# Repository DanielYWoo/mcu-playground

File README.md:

# Projects

## Arduino Robot with RF24L01 remote control

- arduino-robot-1 for the robot
- arduino-robot-1-rc for the remote controller

## Auto watering system

- arduino-watering-1

## Otto (zhamao)

- arduino-zhamao

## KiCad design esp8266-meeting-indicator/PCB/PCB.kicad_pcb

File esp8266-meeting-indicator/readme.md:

## pins

LED:
two 74HC595N
- D0 to 11, shift clock
- D1 to 12, storage latch
- D2 to 14, serial data input

# LED matrix pins
https://www.hackster.io/shahbaz75sb/8x8-led-matrix-interfacing-with-arduino-daec65

Sound Sensor
- D3

Buzzer
- D4

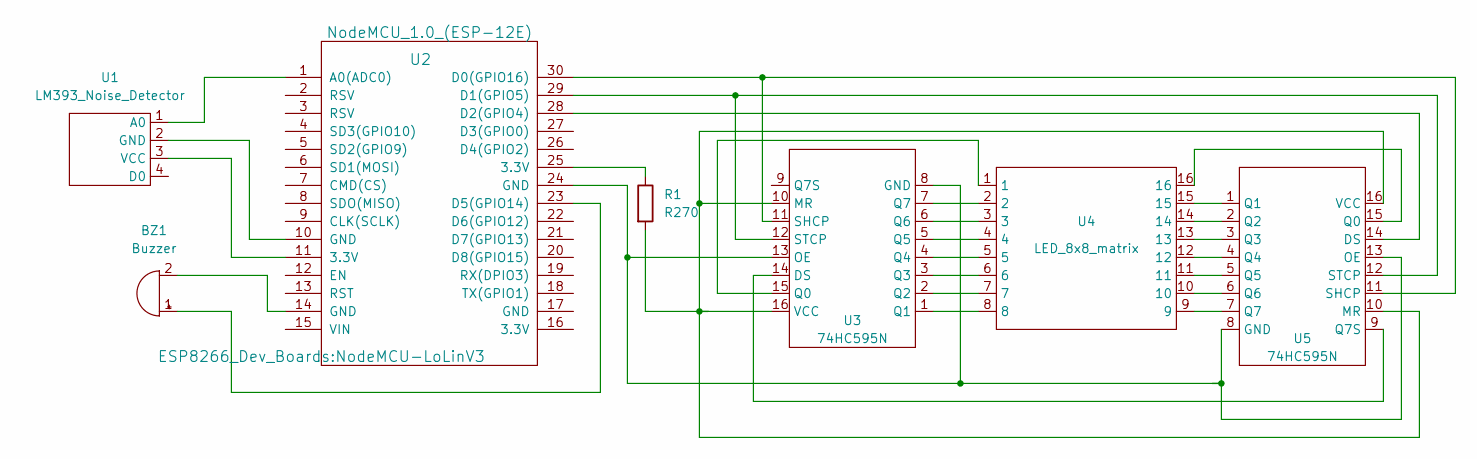
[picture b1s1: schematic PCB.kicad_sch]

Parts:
BZ1: Buzzer; Buzzer_12x9.5RM7.6
R1: R270; R_Axial_DIN0207_L6.3mm_D2.5mm_P10.16mm_Horizontal
U1: LM393_Noise_Detector; PinSocket_1x04_P2.54mm_Vertical
U2: NodeMCU_1.0_(ESP-12E); NodeMCU-LoLinV3
U3, U5: 74HC595N; DIP-16_W7.62mm
U4: LED_8x8_matrix; LED_Matrix_1088

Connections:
unnamed: BZ1.1 (-), U2.23 (D5(GPIO14))
unnamed: BZ1.2 (+), U2.14 (GND)
unnamed: R1.1, U2.25 (3.3V)
unnamed: R1.2, U3.10 (MR), U3.16 (VCC), U5.10 (MR), U5.16 (VCC)
unnamed: U1.1 (A0), U2.1 (A0(ADC0))
unnamed: U1.2 (GND), U2.10 (GND)
unnamed: U1.3 (VCC), U2.11 (3.3V)
unnamed: U2.24 (GND), U3.8 (GND), U3.13 (OE), U5.8 (GND), U5.13 (OE)
unnamed: U2.28 (D2(GPIO4)), U5.14 (DS)
unnamed: U2.29 (D1(GPIO5)), U3.12 (STCP), U5.12 (STCP)
unnamed: U2.30 (D0(GPIO16)), U3.11 (SHCP), U5.11 (SHCP)
unnamed: U3.1 (Q1), U4.8
unnamed: U3.2 (Q2), U4.7
unnamed: U3.3 (Q3), U4.6
unnamed: U3.4 (Q4), U4.5
unnamed: U3.5 (Q5), U4.4
unnamed: U3.6 (Q6), U4.3
unnamed: U3.7 (Q7), U4.2
unnamed: U3.14 (DS), U5.9 (Q7S)
unnamed: U3.15 (Q0), U4.1
unnamed: U4.9, U5.7 (Q7)
unnamed: U4.10, U5.6 (Q6)
unnamed: U4.11, U5.5 (Q5)
unnamed: U4.12, U5.4 (Q4)
unnamed: U4.13, U5.3 (Q3)
unnamed: U4.14, U5.2 (Q2)
unnamed: U4.15, U5.1 (Q1)
unnamed: U4.16, U5.15 (Q0)

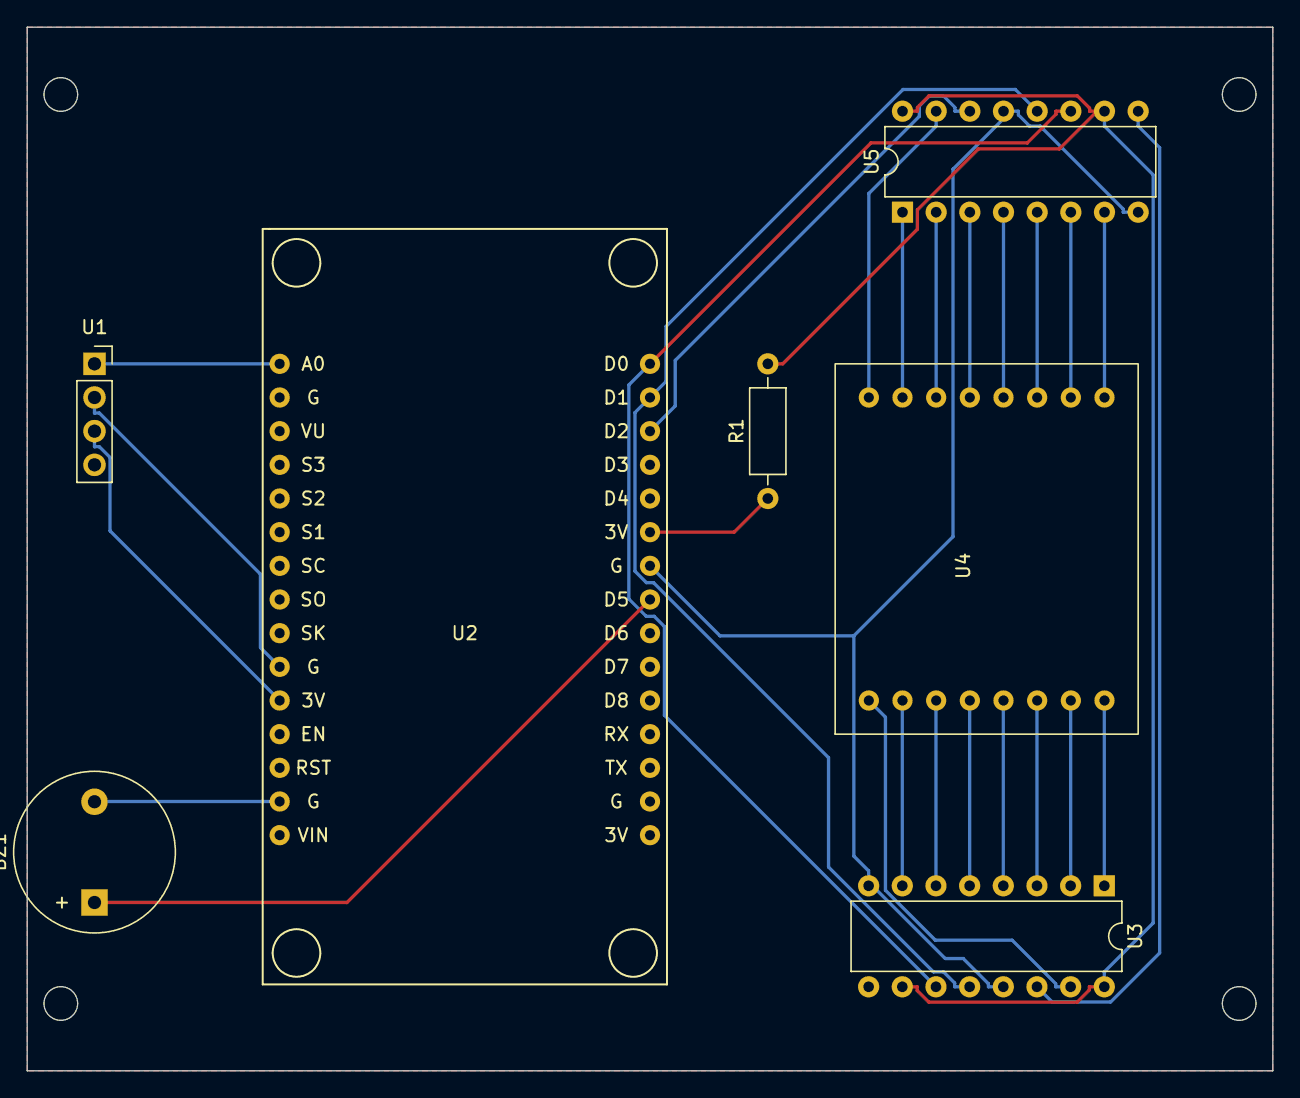
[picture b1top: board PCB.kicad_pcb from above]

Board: 2 copper layers, 94.0 x 78.7 mm, 7 parts (0 on the bottom side), 28 nets.

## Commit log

2015-11-03 init
2019-12-26 new start
2019-12-27 long term plan for pins
2019-12-28 pins change
2019-12-29 separate rc and robot code
2019-12-30 re-layout
2019-12-31 lcd control works now
2020-01-01 now joy stick get fixed, kalman filter does not work
2020-01-04 2.4g
2020-01-04 refactor communication protocol
2020-01-04 595 drive
2020-01-04 rc move
2020-01-04 add serial switch
2020-01-04 next, we need to receive telemetry
2020-01-04 test
2020-01-05 better signal speed
2020-01-05 better 24g speed
2020-01-05 wheel speed telemetry works now
2020-01-05 auto brake almost works
2020-01-05 telemetry
2020-01-05 add servo test cmd
2020-01-05 servo works now
2020-01-06 send ultra sonic back
2020-01-07 add ultra sonic telemetry
2020-01-08 ultrasonic reports negative
2020-01-09 add debug for negative distance, might be battery?
2020-01-09 let dance
2020-01-09 bugfix
2020-01-11 auto pilot
2020-01-11 joystick fix
2020-01-11 ajdust speed
2020-01-11 stick
2020-01-12 rename and refactor
2020-01-12 telemetry to counter
2020-01-15 fix turn
2020-01-19 init watering
2020-01-19 ritchie watering
2020-01-28 my son project
2021-01-10 zhamao
2021-01-19 rename
2022-10-03 readme
2022-10-03 clean
2022-10-08 basic
